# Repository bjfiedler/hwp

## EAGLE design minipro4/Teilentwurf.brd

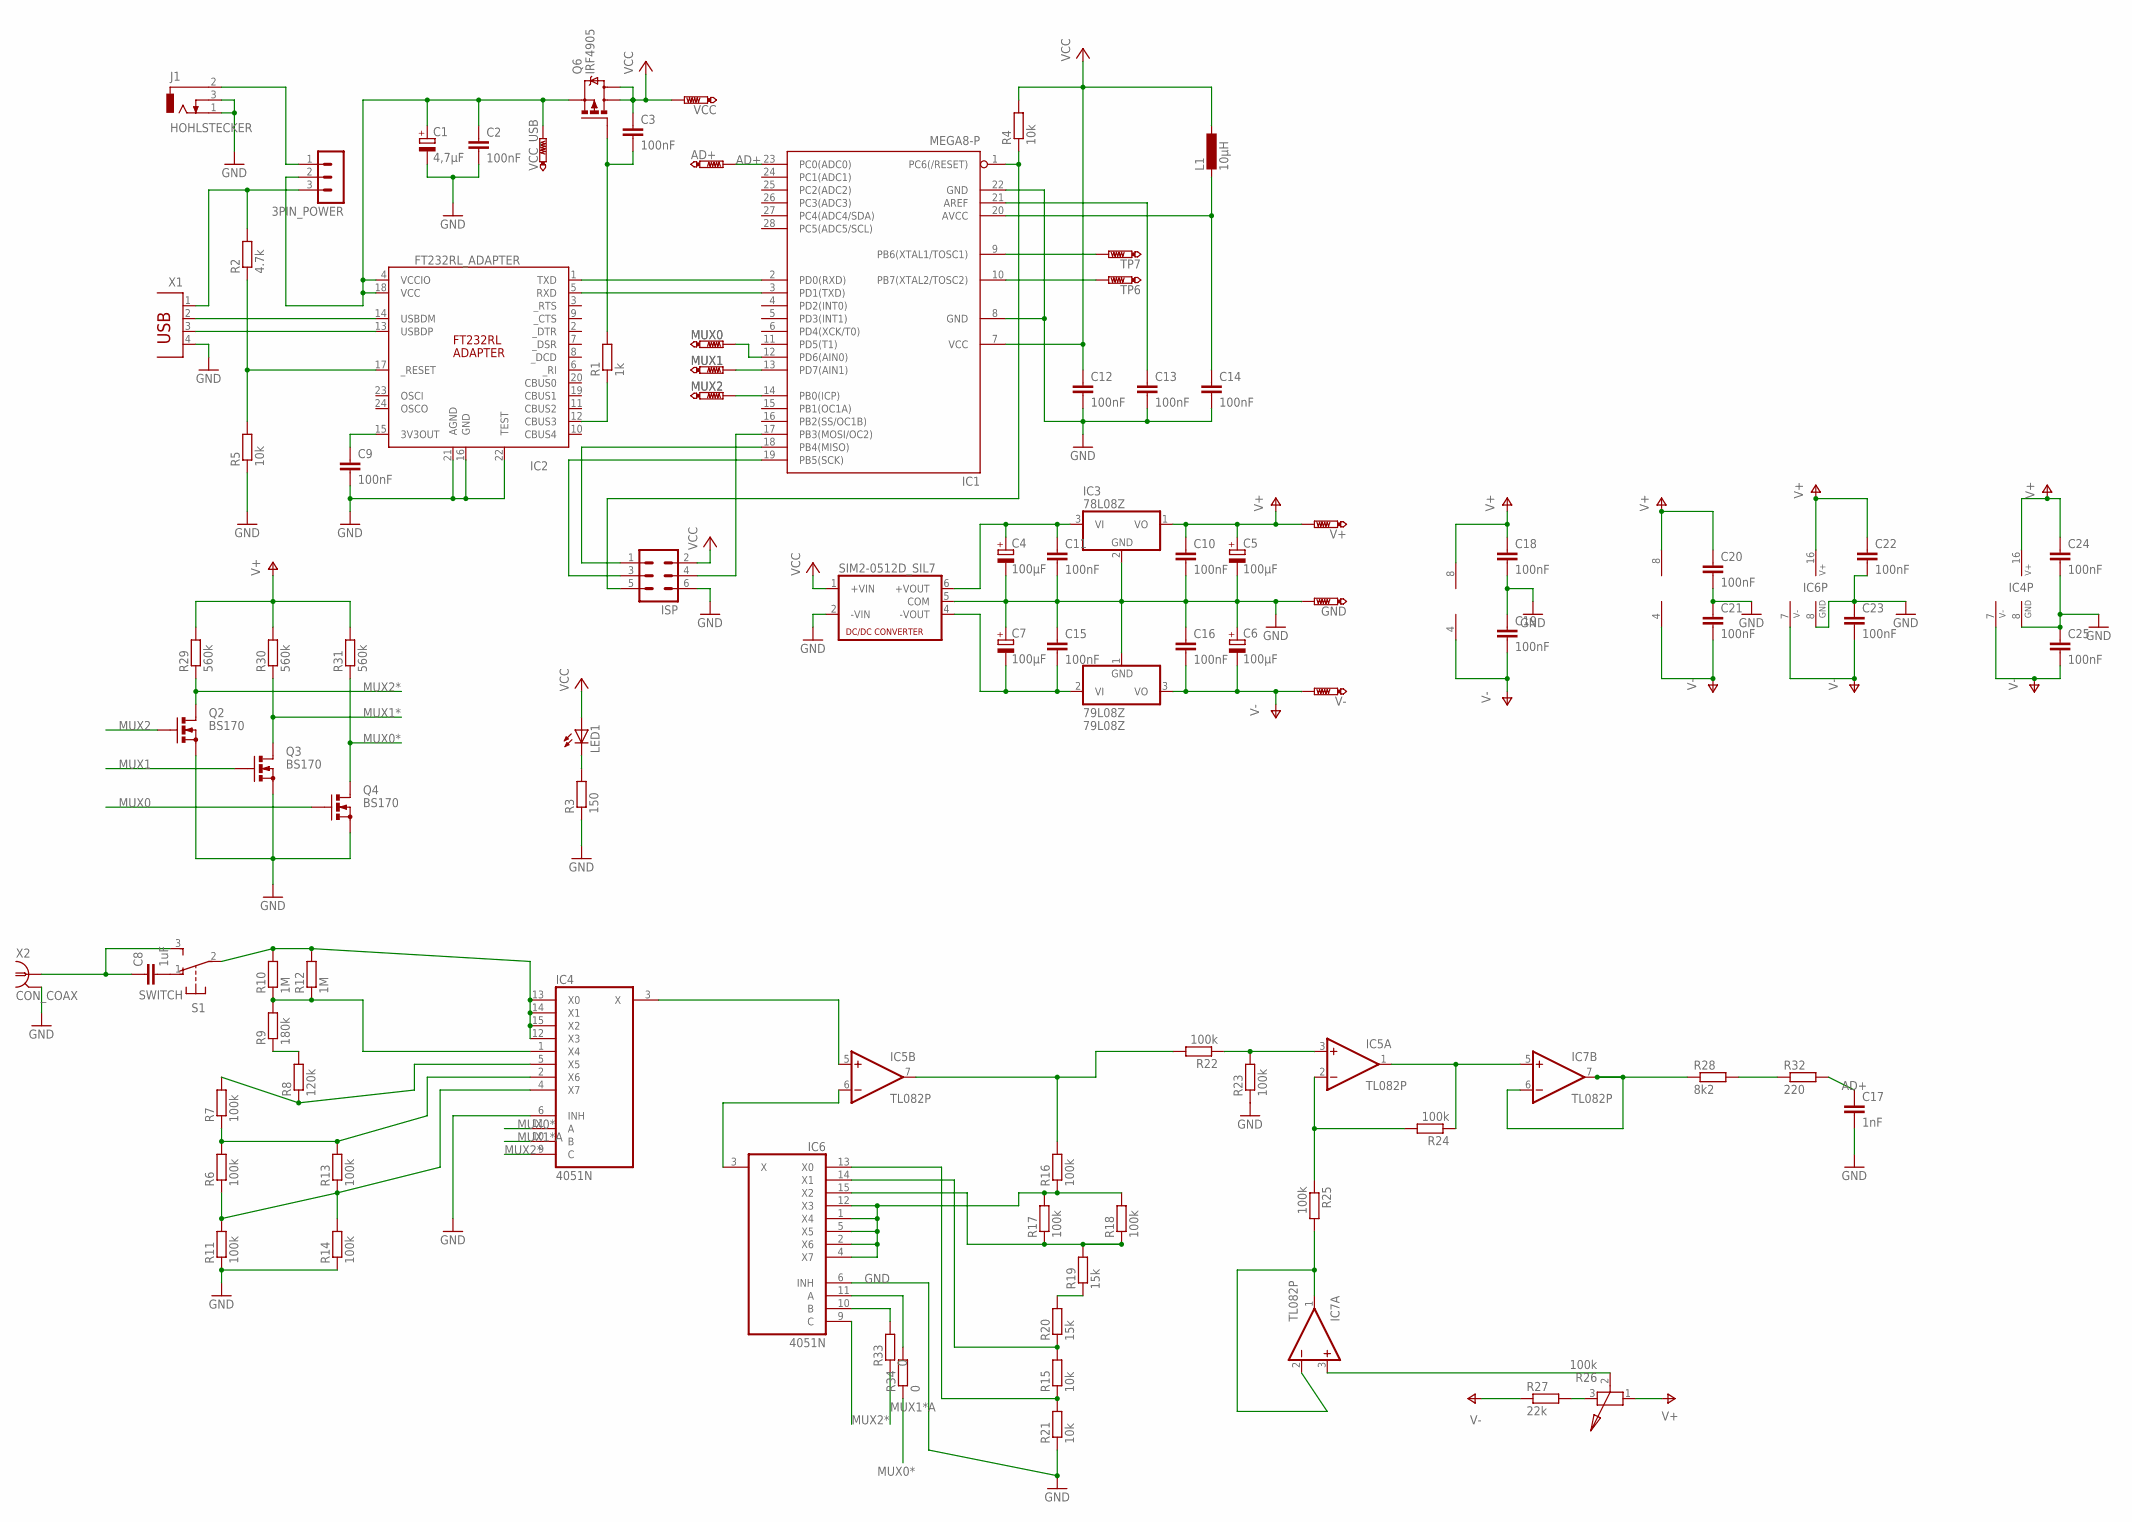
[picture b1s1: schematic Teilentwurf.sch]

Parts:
3PIN_POWER: MA03-1
79L08Z: 79L08Z; TO92
AD+: PTR1PAD1-13Y; P1-13Y
C1: 4,7µF; E2-5
C2, C3, C9, C10, C11, C12, C13, C14, C15, C16, C18, C19, C20, C21, C22, C23, C24, C25: 100nF; C025-030X050
C4, C5, C6, C7: 100µF; E2,5-7
C8: 1uF; C050-050X075
C17: 1nF; C025-030X050
GND: PTR1PAD1-13Y; P1-13Y
IC1: MEGA8-P; DIL28-3
IC2: FT232RL_ADAPTER; DIL24-9
IC3: 78L08Z; TO92
IC4, IC6: 4051N; DIL16
IC5, IC7: TL082P; DIL08
ISP: ML6
J1: HOHLSTECKER; HOHLSTECKER_25
L1: 10µH; 0207/12
LED1: LED3MM
MUX0, MUX1, MUX2: PTR1PAD1-13Y; P1-13Y
Q2, Q3, Q4: BS170; SOT54E
Q6: IRF4905; TO220PAD
R1: 1k; 0207/10
R2: 4.7k; 0207/10
R3: 150; 0207/10
R4: 10k; 0207/12
R5, R15, R21: 10k; 0207/10
R6, R7, R11, R13, R14, R16, R17, R18, R22, R23, R24: 100k; 0207/10
R8: 120k; 0207/10
R9: 180k; 0207/10
R10, R12: 1M; 0207/10
R19, R20: 15k; 0207/10
R25: 100k; 0207/7
R26: 100k; POT
R27: 22k; 0207/10
R28: 8k2; 0207/10
R29, R30, R31: 560k; 0207/10
R32: 220; 0207/15
R33, R34: 0; 0207/10
S1: SWITCH; APEM_5236
SIM2-0512D_SIL7: NMA
TP6, TP7: PTR1PAD1-13Y; P1-13Y
V+: PTR1PAD1-13Y; P1-13Y
V-: PTR1PAD1-13Y; P1-13Y
VCC: PTR1PAD1-13Y; P1-13Y
VCC_USB: PTR1PAD1-13Y; P1-13Y
X1: USB_BUCHSE_B
X2: CON_COAX

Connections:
AD+: AD+.TP, C17.1, IC1.23 (PC0(ADC0)), R32.2
AVCC: C14.1, IC1.20 (AVCC), L1.2
GND: 79L08Z.1 (GND), C1.-, C2.2, C4.-, C5.-, C6.+, C7.+, C9.2, C10.2, C11.2, C12.2, C13.2, C14.2, C15.1, C16.1, C17.2, C18.2, C19.1, C20.2, C21.1, C22.2, C23.1, C24.2, C25.1, GND.TP, IC1.8 (GND), IC1.22 (GND), IC2.16 (GND), IC2.21 (AGND), IC2.22 (TEST), IC3.2 (GND), IC4.6 (INH), IC4.8 (GND), IC6.6 (INH), IC6.8 (GND), ISP.6, J1.1 (3), J1.3 (2), Q2.S, Q3.S, Q4.S, R3.1, R5.1, R11.1, R14.1, R21.1, R23.1, SIM2-0512D_SIL7.2 (-VIN), SIM2-0512D_SIL7.5 (COM), X1.4, X2.G1 (GND), X2.G2 (GND), X2.GND
MUX0: IC1.12 (PD6(AIN0)), MUX0.TP, Q4.G
MUX0*: IC4.11 (A), Q4.D, R31.1, R34.1
MUX1: IC1.13 (PD7(AIN1)), MUX1.TP, Q3.G
MUX1*: IC6.10 (B), Q3.D, R30.1, R33.2
MUX1*A: IC4.10 (B), R33.1
MUX2: IC1.14 (PB0(ICP)), MUX2.TP, Q2.G
MUX2*: IC4.9 (C), IC6.9 (C), Q2.D, R29.1
unnamed: 3PIN_POWER.3, R2.2, X1.1
unnamed: IC1.17 (PB3(MOSI/OC2)), ISP.4
unnamed: C9.1, IC2.15 (3V3OUT)
unnamed: IC1.2 (PD0(RXD)), IC2.1 (TXD)
unnamed: C3.2, Q6.G, R1.2
unnamed: IC1.19 (PB5(SCK)), ISP.3
unnamed: IC2.14 (USBDM), X1.2
unnamed: IC2.13 (USBDP), X1.3
unnamed: IC1.3 (PD1(TXD)), IC2.5 (RXD)
unnamed: IC2.12 (CBUS3), R1.1
unnamed: C4.+, C11.1, IC3.3 (VI), SIM2-0512D_SIL7.6 (+VOUT)
unnamed: IC2.17 (_RESET), R2.1, R5.2
unnamed: IC4.2 (X6), R6.2, R7.1, R13.2
unnamed: 79L08Z.2 (VI), C7.-, C15.2, SIM2-0512D_SIL7.4 (-VOUT)
unnamed: IC1.18 (PB4(MISO)), ISP.1
unnamed: 3PIN_POWER.1, J1.2 (1)
unnamed: IC4.5 (X5), R7.2, R8.1
unnamed: R8.2, R9.1
unnamed: IC4.1 (X4), R9.2, R10.1, R12.1
unnamed: LED1.K (C), R3.2
unnamed: C13.1, IC1.21 (AREF)
unnamed: IC4.4 (X7), R6.1, R11.2, R13.1, R14.2
unnamed: IC6.1 (X4), IC6.2 (X6), IC6.4 (X7), IC6.5 (X5), IC6.12 (X3), R16.1, R17.2, R18.2
unnamed: IC4.12 (X3), IC4.13 (X0), IC4.14 (X1), IC4.15 (X2), R10.2, R12.2, S1.2
unnamed: IC4.3 (X), IC5.5 (+IN)
unnamed: IC5.6 (-IN), IC6.3 (X)
unnamed: IC5.3 (+IN), R22.1, R23.2
unnamed: R19.1, R20.2
unnamed: C8.2, S1.1 (O)
unnamed: C8.1, S1.3 (S), X2.1
unnamed: IC6.13 (X0), R15.1, R21.2
unnamed: IC6.14 (X1), R15.2, R20.1
unnamed: IC6.15 (X2), R17.1, R18.1, R19.2
unnamed: IC5.7 (OUT), R16.2, R22.2
unnamed: IC5.1 (OUT), IC7.5 (+IN), R24.1
unnamed: IC5.2 (-IN), R24.2, R25.1
unnamed: IC7.1 (OUT), IC7.2 (-IN), R25.2
unnamed: R26.3 (2), R27.2
unnamed: IC7.3 (+IN), R26.2 (3)
unnamed: IC7.6 (-IN), IC7.7 (OUT), R28.1
unnamed: R28.2, R32.1
unnamed: IC1.10 (PB7(XTAL2/TOSC2)), TP6.TP
unnamed: IC1.9 (PB6(XTAL1/TOSC1)), TP7.TP
unnamed: IC6.11 (A), R34.2
RESET: IC1.1 (PC6(/RESET)), ISP.5, R4.1
V+: C5.+, C10.1, C18.1, C20.1, C22.1, C24.1, IC3.1 (VO), IC4.16 (V+), IC5.8 (V+), IC6.16 (V+), IC7.8 (V+), R26.1, R29.2, R30.2, R31.2, V+.TP
V-: 79L08Z.3 (VO), C6.-, C16.2, C19.2, C21.2, C23.2, C25.2, IC4.7 (V-), IC5.4 (V-), IC6.7 (V-), IC7.4 (V-), R27.1, V-.TP
VCC: C3.1, C12.1, IC1.7 (VCC), ISP.2, L1.1, LED1.A, Q6.D, Q6.D2 (D), R4.2, SIM2-0512D_SIL7.1 (+VIN), VCC.TP
VCC_USB: 3PIN_POWER.2, C1.+, C2.1, IC2.4 (VCCIO), IC2.18 (VCC), Q6.S, VCC_USB.TP

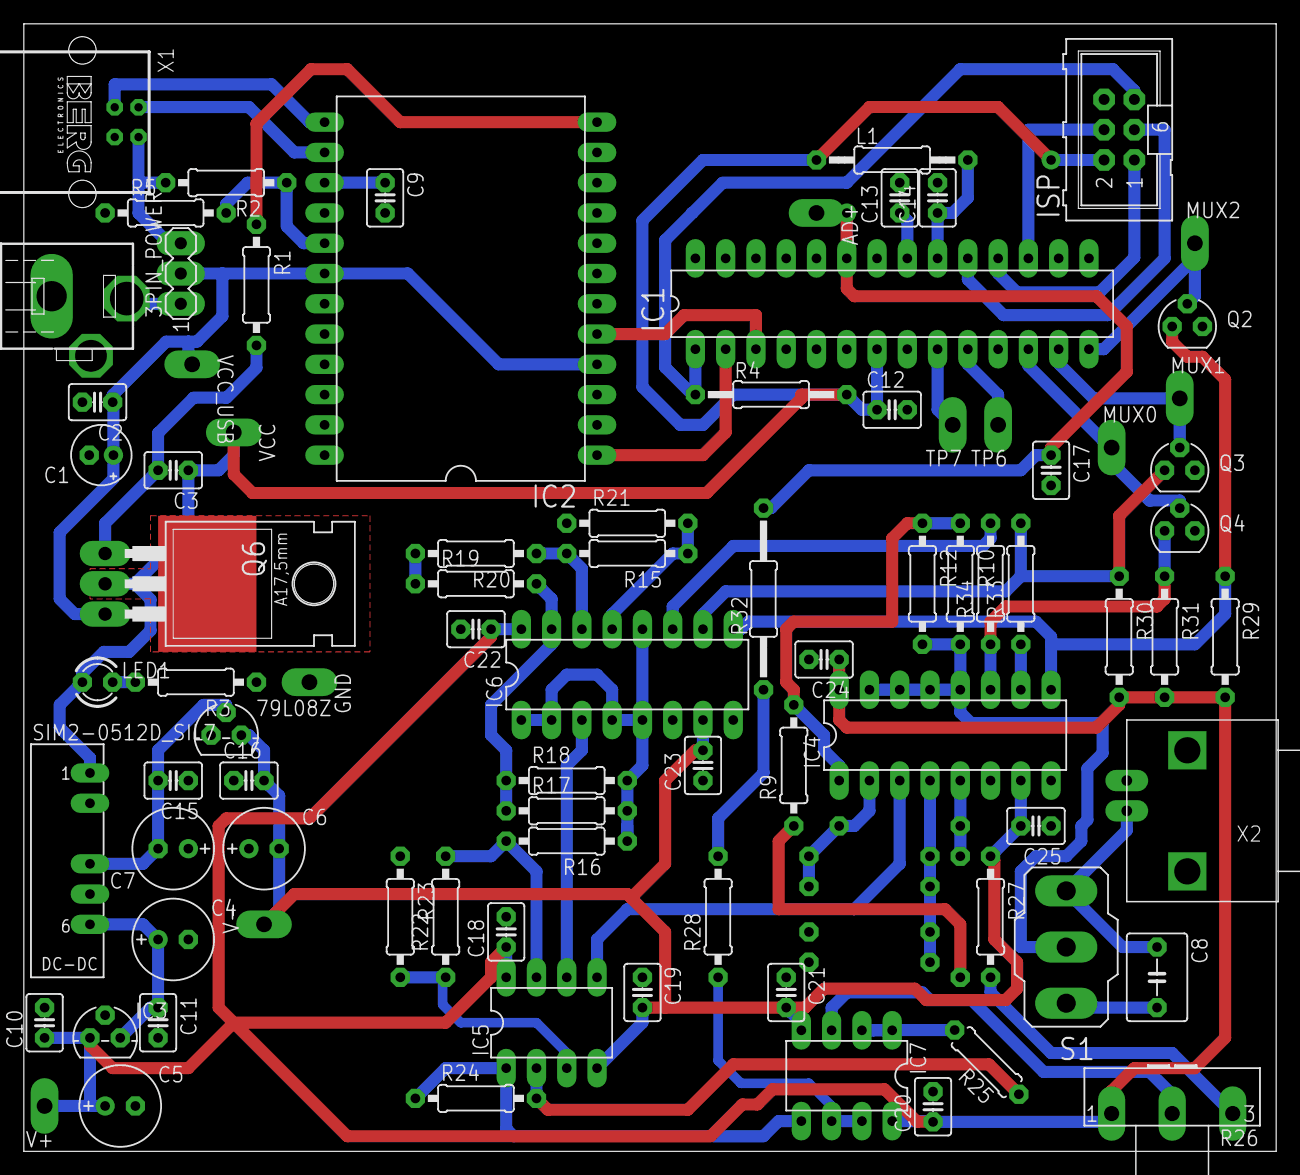
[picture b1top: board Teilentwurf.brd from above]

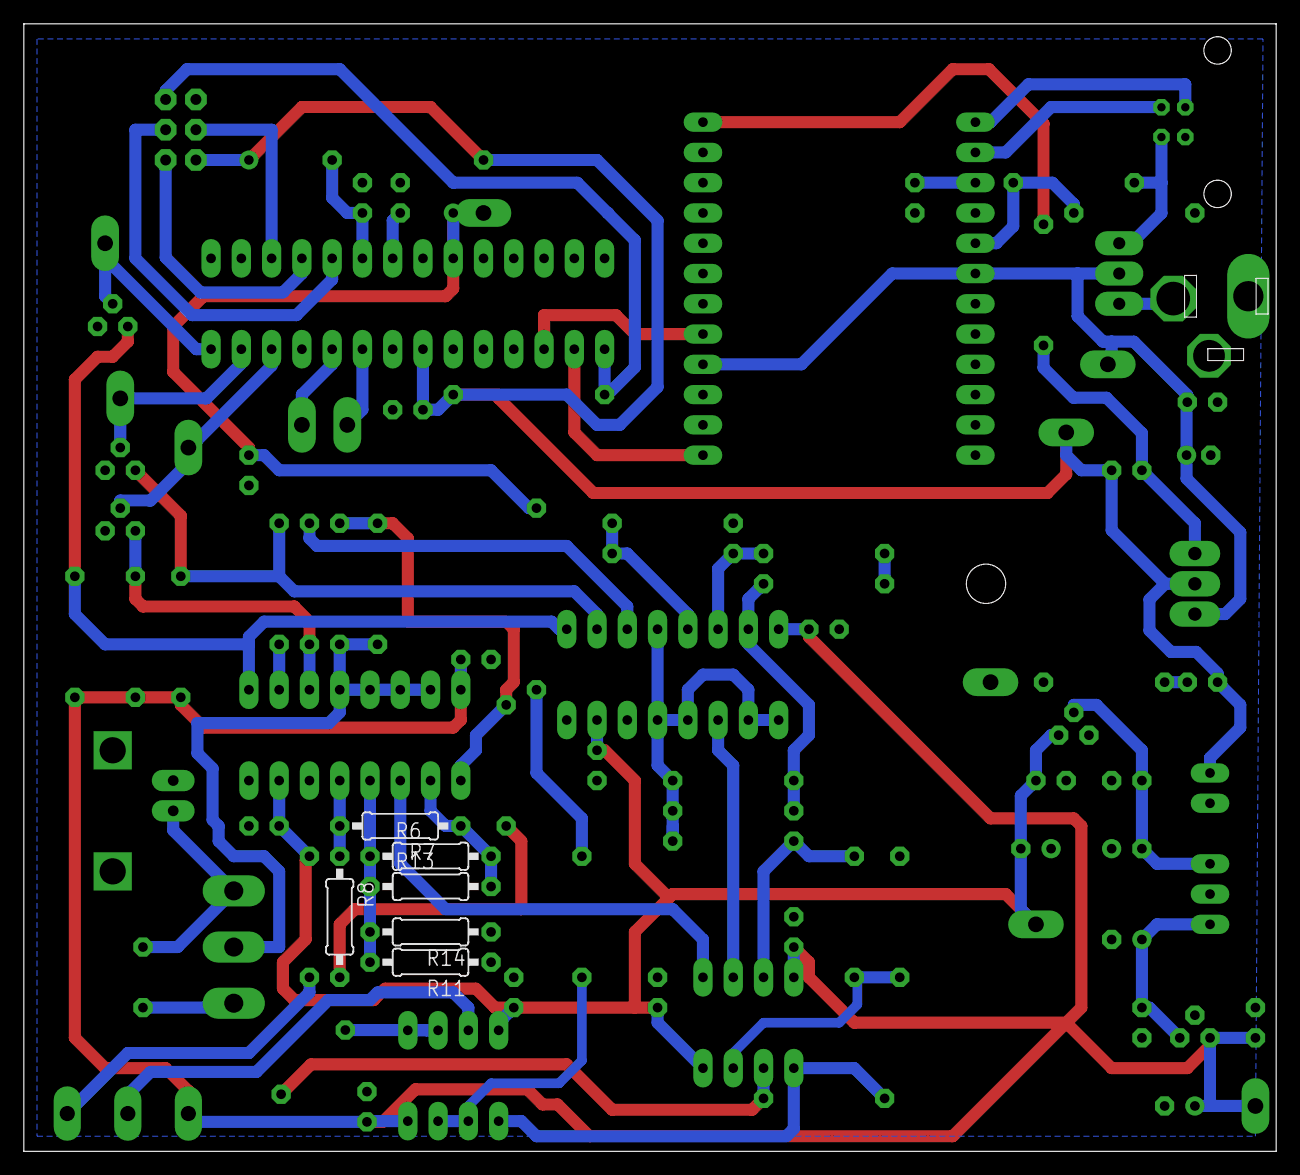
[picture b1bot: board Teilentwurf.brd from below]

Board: 2 copper layers, 105.1 x 94.6 mm, 91 parts (6 on the bottom side), 59 nets.

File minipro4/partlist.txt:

Partlist

Exported from Teilentwurf.sch at 25.04.2014 17:44:07

EAGLE Version 6.5.0 Copyright (c) 1988-2013 CadSoft

Assembly variant: 

Part            Value           Device          Package        Library           Sheet

3PIN_POWER                      MA03-1          MA03-1         03_device-library 1
79L08Z          79L08Z          79L08Z          TO92           03_device-library 1
AD+             PTR1PAD1-13Y    PTR1PAD1-13Y    P1-13Y         03_device-library 1
C1              4,7µF           CPOL-EUE2-5     E2-5           03_device-library 1
C2              100nF           C-EU025-030X050 C025-030X050   03_device-library 1
C3              100nF           C-EU025-030X050 C025-030X050   03_device-library 1
C4              100µF           CPOL-EUE2.5-7   E2,5-7         03_device-library 1
C5              100µF           CPOL-EUE2.5-7   E2,5-7         03_device-library 1
C6              100µF           CPOL-EUE2.5-7   E2,5-7         03_device-library 1
C7              100µF           CPOL-EUE2.5-7   E2,5-7         03_device-library 1
C8              1uF             C-EU050-050X075 C050-050X075   03_device-library 1
C9              100nF           C-EU025-030X050 C025-030X050   03_device-library 1
C10             100nF           C-EU025-030X050 C025-030X050   03_device-library 1
C11             100nF           C-EU025-030X050 C025-030X050   03_device-library 1
C12             100nF           C-EU025-030X050 C025-030X050   03_device-library 1
C13             100nF           C-EU025-030X050 C025-030X050   03_device-library 1
C14             100nF           C-EU025-030X050 C025-030X050   03_device-library 1
C15             100nF           C-EU025-030X050 C025-030X050   03_device-library 1
C16             100nF           C-EU025-030X050 C025-030X050   03_device-library 1
C17             1nF             C-EU025-030X050 C025-030X050   03_device-library 1
C18             100nF           C-EU025-030X050 C025-030X050   03_device-library 1
C19             100nF           C-EU025-030X050 C025-030X050   03_device-library 1
C20             100nF           C-EU025-030X050 C025-030X050   03_device-library 1
C21             100nF           C-EU025-030X050 C025-030X050   03_device-library 1
C22             100nF           C-EU025-030X050 C025-030X050   03_device-library 1
C23             100nF           C-EU025-030X050 C025-030X050   03_device-library 1
C24             100nF           C-EU025-030X050 C025-030X050   03_device-library 1
C25             100nF           C-EU025-030X050 C025-030X050   03_device-library 1
GND             PTR1PAD1-13Y    PTR1PAD1-13Y    P1-13Y         03_device-library 1
IC1             MEGA8-P         MEGA8-P         DIL28-3        03_device-library 1
IC2             FT232RL_ADAPTER FT232RL_ADAPTER DIL24-9        03_device-library 1
IC3             78L08Z          78L08Z          TO92           03_device-library 1
IC4             4051N           4051N           DIL16          03_device-library 1
IC5             TL082P          TL082P          DIL08          03_device-library 1
IC6             4051N           4051N           DIL16          03_device-library 1
IC7             TL082P          TL082P          DIL08          03_device-library 1
ISP                             ML6             ML6            03_device-library 1
J1              HOHLSTECKER     HOHLSTECKER     HOHLSTECKER_25 03_device-library 1
L1              10µH            L-EU0207/12     0207/12        03_device-library 1
LED1                            LED3MM          LED3MM         03_device-library 1
MUX0            PTR1PAD1-13Y    PTR1PAD1-13Y    P1-13Y         03_device-library 1
MUX1            PTR1PAD1-13Y    PTR1PAD1-13Y    P1-13Y         03_device-library 1
MUX2            PTR1PAD1-13Y    PTR1PAD1-13Y    P1-13Y         03_device-library 1
Q2              BS170           BS170           SOT54E         03_device-library 1
Q3              BS170           BS170           SOT54E         03_device-library 1
Q4              BS170           BS170           SOT54E         03_device-library 1
Q6              IRF4905         IRF4905PBF      TO220PAD       03_device-library 1
R1              1k              R-EU_0207/10    0207/10        03_device-library 1
R2              4.7k            R-EU_0207/10    0207/10        03_device-library 1
R3              150             R-EU_0207/10    0207/10        03_device-library 1
R4              10k             R-EU_0207/12    0207/12        03_device-library 1
R5              10k             R-EU_0207/10    0207/10        03_device-library 1
R6              100k            R-EU_0207/10    0207/10        03_device-library 1
R7              100k            R-EU_0207/10    0207/10        03_device-library 1
R8              120k            R-EU_0207/10    0207/10        03_device-library 1
R9              180k            R-EU_0207/10    0207/10        03_device-library 1
R10             1M              R-EU_0207/10    0207/10        03_device-library 1
R11             100k            R-EU_0207/10    0207/10        03_device-library 1
R12             1M              R-EU_0207/10    0207/10        03_device-library 1
R13             100k            R-EU_0207/10    0207/10        03_device-library 1
R14             100k            R-EU_0207/10    0207/10        03_device-library 1
R15             10k             R-EU_0207/10    0207/10        03_device-library 1
R16             100k            R-EU_0207/10    0207/10        03_device-library 1
R17             100k            R-EU_0207/10    0207/10        03_device-library 1
R18             100k            R-EU_0207/10    0207/10        03_device-library 1
R19             15k             R-EU_0207/10    0207/10        03_device-library 1
R20             15k             R-EU_0207/10    0207/10        03_device-library 1
R21             10k             R-EU_0207/10    0207/10        03_device-library 1
R22             100k            R-EU_0207/10    0207/10        03_device-library 1
R23             100k            R-EU_0207/10    0207/10        03_device-library 1
R24             100k            R-EU_0207/10    0207/10        03_device-library 1
R25             100k            R-EU_0207/7     0207/7         resistor          1
R26             100k            POT             POT            03_device-library 1
R27             22k             R-EU_0207/10    0207/10        03_device-library 1
R28             8k2             R-EU_0207/10    0207/10        03_device-library 1
R29             560k            R-EU_0207/10    0207/10        03_device-library 1
R30             560k            R-EU_0207/10    0207/10        03_device-library 1
R31             560k            R-EU_0207/10    0207/10        03_device-library 1
R32             220             R-EU_0207/15    0207/15        03_device-library 1
R33             0               R-EU_0207/10    0207/10        03_device-library 1
R34             0               R-EU_0207/10    0207/10        03_device-library 1
S1              SWITCH          SWITCH          APEM_5236      03_device-library 1
SIM2-0512D_SIL7                 NMA             NMA            03_device-library 1
TP6             PTR1PAD1-13Y    PTR1PAD1-13Y    P1-13Y         03_device-library 1
TP7             PTR1PAD1-13Y    PTR1PAD1-13Y    P1-13Y         03_device-library 1
V+              PTR1PAD1-13Y    PTR1PAD1-13Y    P1-13Y         03_device-library 1
V-              PTR1PAD1-13Y    PTR1PAD1-13Y    P1-13Y         03_device-library 1
VCC             PTR1PAD1-13Y    PTR1PAD1-13Y    P1-13Y         03_device-library 1
VCC_USB         PTR1PAD1-13Y    PTR1PAD1-13Y    P1-13Y         03_device-library 1
X1                              USB_BUCHSE_B    USB_BUCHSE_B   03_device-library 1
X2              CON_COAX        CON_COAX        CON_COAX       03_device-library 1

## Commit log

2013-12-20 init
2014-01-01 + ‘.sparkleshare’ + ‘SparkleShare.txt’
2014-01-02 + ‘simulationen/c12.dpl’ + ‘simulationen/c12.sch’ + ‘simulationen/c13.dpl’ + ‘simulationen/c13.sch’ + ‘simulationen/c14.dpl’ + ‘simulationen/c14.sch’ + ‘simulationen/c15.dpl’ + ‘simulationen/c15.sch’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
2014-01-02 / ‘PM_Template_v3.xls’
2014-01-03 erste punkte von c1.1
2014-01-07 + ‘test.txt’
2014-01-07 - ‘test.txt’
2014-01-07 + ‘6.3.pdf’
2014-01-07 / ‘6.3.pdf’
2014-01-07 + ‘simulationen/c12.dat’
2014-01-07 + ‘simulationen/c17.dat’
2014-01-07 / ‘simulationen/c17.sch’
2014-01-07 + ‘simulationen/c15.dat’
2014-01-08 foo bar
2014-01-08 fehlende dateien hinzugefuegt
2014-01-08 / ‘C11-erster-punkt.pdf’
2014-01-08 / ‘simulationen/entwurf.dat’
2014-01-08 / ‘simulationen/entwurf.dpl’ / ‘simulationen/entwurf.sch’
2014-01-08 / ‘simulationen/entwurf.sch’
2014-01-09 Tiefpass 2. Ordnung hinzugefügt
2014-01-10 + ‘PM_Template_v3.accdb’
2014-01-13 + ‘6.3.mht’
2014-01-13 neuer aufbau mit doppel mux
2014-01-13 - ‘PM_Template_v3.accdb’
2014-01-13 / ‘simulationen/entwurf.dat’ / ‘simulationen/entwurf.dpl’ / ‘simulationen/entwurf.sch’
2014-01-22 + ‘minipro4/Teilentwurf.b##’ + ‘minipro4/Teilentwurf.s##’
2014-01-22 / ‘minipro4/Teilentwurf.b##’ / ‘minipro4/Teilentwurf.s##’
2014-01-22 < ‘minipro4/Teilentwurf.b##’ > ‘minipro4/Teilentwurf.b#1’ / ‘minipro4/Teilentwurf.brd’ < ‘minipro4/Teilentwurf.s##’ > ‘minipro4/Teilentwurf.s#1’ / ‘minipro4/Teilentwurf.sch’
2014-01-22 / ‘minipro4/Teilentwurf.s##’
2014-01-22 / ‘minipro4/Teilentwurf.b#1’ < ‘minipro4/Teilentwurf.b##’ > ‘minipro4/Teilentwurf.b#2’ / ‘minipro4/Teilentwurf.brd’ / ‘minipro4/Teilentwurf.s#1’ < ‘minipro4/Teilentwurf.s##’ > ‘minipro4/Teilentwurf.s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
2014-01-22 nvdsjbjisd
2014-01-22 dadsadsaasd
2014-01-24 eagle iteration
2014-01-24 Layout
2014-01-24 Added ground plane
2014-01-28 Layout Iteration
2014-01-29 Präsentation
2014-04-25 added partlist.txt
2014-05-07 Winkel überarbeitet
